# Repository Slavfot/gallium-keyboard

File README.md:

## Gallium Keyboard

The Gallium Keyboard is a Wireless Ergonomical Split Keyboard.

# DISCLAIMER

I have a problem with the keyboard that i have opened an issue at the redox Github. https://github.com/mattdibi/redox-keyboard/issues/55
The problem is interference making it hard to use in some environments.
I use it daily at work and it works really good except sometimes i have to replug the usb receiver at startup to get a good connection.
At home it is almost unusable because of interference. Missing key presses and high latency.
I'm trying to solve this and will post an update when i find a stable solution for the wireless communication.

# Future
At the moment I'm working on a micro pro version wich will make it possible to use the nice!nano bluetooth module with it instead.
My goal is to stock these and sell as kits togehter with 3D printed case. And even aluminium cases in GB.

## Summary

  - [Bill of materials](#bill-of-materials)
  - [Transmitters Assembly](#transmitters-assembly)
  - [Receiver Assembly](#receiver-assembly)
  - [Firmware](#firmware)
  - [Battery usage](#battery-usage)

## Bill of materials

#### Transmitters

| Qty | Item                                          | Notes                                               |
|----:|-----------------------------------------------|-----------------------------------------------------|
|  62 | Cherry MX compatible switches                 |                                                     |
|  62 | Kailh MX hot swap sockets (optional)          |                                                     |
|   2 | Gallium Wireless PCBs                         |                                                     |
|   2 | YJ-14015 modules (Core51822B clones)          | [aliexpress or ebay](https://www.aliexpress.com/item/NRF51822-Core51822-BLE-4-0-Bluetooth-2-4G-Wireless-Module-Antenna-Board-For-ULP-SPI-I2C/32842154172.html?spm=2114.search0104.3.8.663a616aYeRlVr&ws_ab_test=searchweb0_0,searchweb201602_1_10065_10068_10843_10059_10884_10887_10696_100031_10084_10083_10103_10618_10304_10307_10820_10821_10302,searchweb201603_60,ppcSwitch_5&algo_expid=1dded059-5054-4890-bcc4-6face1150a21-1&algo_pvid=1dded059-5054-4890-bcc4-6face1150a21&priceBeautifyAB=0)
|  62 | 1N4148 diodes                                 | SMD 1N4148 SOD-123 diodes can also be used          |
|   2 | Keystone 3034 SMT battery holders             | [digikey](https://www.digikey.com/product-detail/en/keystone-electronics/3034/36-3034-ND/4499289)|
|   2 | PCM12SMTR SMT slide switches                  | [digikey](https://www.digikey.com/product-detail/en/c-k/PCM12SMTR/401-2016-1-ND/1640125)|
|   2 | Right angle 0.1" header (1x4pin)              |                                                     |

#### Receiver

| Qty | Item                                          | Notes                                               |
|----:|-----------------------------------------------|-----------------------------------------------------|
|   1 | Redox receiver PCB                            |                                                     |
|   1 | YJ-14015 module (Core51822B clone)            | [aliexpress or ebay](https://www.aliexpress.com/item/NRF51822-Core51822-BLE-4-0-Bluetooth-2-4G-Wireless-Module-Antenna-Board-For-ULP-SPI-I2C/32842154172.html?spm=2114.search0104.3.8.663a616aYeRlVr&ws_ab_test=searchweb0_0,searchweb201602_1_10065_10068_10843_10059_10884_10887_10696_100031_10084_10083_10103_10618_10304_10307_10820_10821_10302,searchweb201603_60,ppcSwitch_5&algo_expid=1dded059-5054-4890-bcc4-6face1150a21-1&algo_pvid=1dded059-5054-4890-bcc4-6face1150a21&priceBeautifyAB=0) |
|   1 | Arduino 5v 16MHz Pro Micro compatible microcontroller  | [aliexpress or ebay]                                |
|   1 | 1117 3.3v regulator in SOT223                 | [digikey](https://www.digikey.com/product-detail/en/diodes-incorporated/AZ1117IH-3.3TRG1/AZ1117IH-3.3TRG1DICT-ND/5699682)|
|   2 | 330 Ohm 0805(2012 metric) SMD resistors       | Default configuration. Values depends on LED color, see [below](#resistor-values)|
|   2 | 220 Ohm 0805(2012 metric) SMD resistors       | Default configuration. Values depends on LED color, see [below](#resistor-values)|
|   3 | 1.5k Ohm 0805(2012 metric) SMD resistors      | Default configuration. See [below](#resistor-values)|
|   1 | Red 0805(2012 metric) SMD standard LED        | Default configuration.                              |
|   1 | Blue 0805(2012 metric) SMD standard LED       | Default configuration.                              |
|   1 | Green 0805(2012 metric) SMD standard LED      | Default configuration.                              |
|   1 | White 0805(2012 metric) SMD standard LED      | Default configuration.                              |
|   1 | Through hole momentary switch                 | Dimensions 6mm x 6mm x 4.3mm                        |
|   1 | Right angle 0.1" header (1x4pin)              |                                                     |
|   2 | Straight hot swap 0.1" header (1x6pin)        | Use wire from diods as legs                         |

> :information_source: You can also use the [Mitosis receiver](https://github.com/reversebias/mitosis-hardware/blob/master/bom/README.md) since it's almost identical, or you can build a receiver on your own. 

> :warning: To program the YJ-14015 MCUs you need an ST-Link v2 programmer, these can be found on eBay or Aliexpress for as little as 2$ shipped. See [picture below](#nordic-mcus-firmware).

##### Resistor values

If you want to customize your LEDs color or save a few bucks by ordering the LED all the same color you can refer to this section for choosing the correct resistor values. Otherwise you can refer to the [default configuration](#default-configuration).

There are two sets of resistor that you need for the receiver.

- The voltage divider resistors (`R1`, `R2` and `R3`): anything between 1.5k Ohm and 4.7k Ohm is good.
- The LEDs resistors (`R4`,`R6`,`R7` and `R8`): see the following table.

| LED color | Vf   | Suggested resistor value |
|-----------|------|--------------------------|
| Red       | 1.7V | 330 Ohm                  |
| Yellow    | 2.1V | 330 Ohm                  |
| Blue      | 3.2V | 220 Ohm                  |
| Green     | 2.2V | 330 Ohm                  |
| White     | 3.6V | 220 Ohm                  |

Depending on the color you choose to use you should use the resistor listed above.

#### Default configuration

Here you can find the default configuration for the receiver assembly.

| Label | Component         |
|-------|-------------------|
| D1    | Red LED           |
| D2    | Blue LED          |
| D3    | Green LED         |
| D4    | White LED         |
| R4    |  330 Ohm resistor |
| R6    |  220 Ohm resistor |
| R7    |  330 Ohm resistor |
| R8    |  220 Ohm resistor |
| R1    | 1.5k Ohm resistor |
| R2    | 1.5k Ohm resistor |
| R3    | 1.5k Ohm resistor |

## Transmitters Assembly

Assembly steps:

- Solder components to PCBs.
  1. Solder slider switch. 
  2. Solder the YJ-14015 on the same side as the slider switch.
  3. Solder 1N4148 diodes either SMT or THT (Surface-mount Technology or Through-hole Technology).
  4. Apply insulating tape over the pads surrounding the battery ground pad before soldering the battery holder [picture below](#battery-holder-installation-detail).
  5. Some solder is needed on the ground pad to contact properly with the battery. See [picture below](#battery-holder-installation-detail).
  6. Solder the battery holders.
  7. If you use the onboard CR2032 battery holder then bridge the jumper JP_BAT1 to either R or L depending on wich side the battery is located on. See [picture below](#bridge-jumper).
     (This is not needed if you use external battery pinout EXT-BAT)
  8. Solder the programming headers.
  9. (Optional) Solder Kailh Hot Swap Sockets
- Fit the PCBs inside their cases.
- Add the switches to the plate.
- Solder switches to the PCB.
- Add the CR2032 batteries.
- Program the MCUs.
- Close the case.

##### How i solder surface mount components:
Wet one pad with solder.
Position the component and hold the component in place with a tweezer.
Heat up the wet pad and let cool, this should fix the component.
Re-heat and adjust the position if the component isn't placed perfect.
Be sure not to heat to long wich may damage the PCB or the component.
Solder the rest of the pads like normal.

##### Programming headers detail:

##### MCUs detail:

##### Slider switch detail:

##### Diodes installation detail:

SMT on the left and THT on the right.

##### Battery holder installation detail:

##### Left and right hand completed assembly:

##### Assembled PCB:

## Receiver Assembly

The receiver assembly is pretty straightforward i suggest soldering it in this order:

1. Solder D1, D2, D3 and D4 LEDs. See [image](#leds-installation-detail) for orientation.
2. Solder R4, R6, R7 and R8 resistors.
3. Solder R1, R2 and R3 resistors.
4. Solder the AMS1117.
5. Solder the programming headers. I suggest you to cut the excess of the header **before** soldering the headers. You should stay as flush to the PCB surface as possible since the controller will be soldered above the headers. Use some masking tape to help you keep the header in place while soldering.
6. Solder the Arduino Pro Micro headers.
7. Solder the YJ-14015. I suggest you to glue it in place or use some masking tape to help you during soldering.
8. Solder the reset button.
9. Upload the firmware and you're done.

##### Assembled PCB, front:

##### Assembled PCB, back:

##### LEDs installation detail:

> :information_source: Please note that here I installed 220 Ohm resistors because I used only blue and white LEDs as I only had those laying around. You should use the resistor values suggested [here](#resistor-values) or follow the [default configuration](#default-configuration).

## Firmware

**Basics**: The Gallium keyboard works similarly to the [Mitosis keyboard](https://github.com/qmk/qmk_firmware/tree/master/keyboards/mitosis): we have two transmitters responsible for scanning the two matrices, which then transmit the matrix status through the [Gazel protocol](https://developer.nordicsemi.com/nRF5_SDK/nRF51_SDK_v5.x.x/doc/5.2.0/html/a00140.html) to the receiver. The receiver is another YJ-14015 which receives the two matrix scans and send it through serial to the Arduino Pro Micro. The Pro Micro is responsible for running QMK and converting the bytes received by the YJ-14015 into actual keystrokes.

Firmware sources available here: [https://github.com/slavfot/gallium-firmware](https://github.com/slavfot/gallium-firmware).

You'll need to upload the firmware to the corresponding MCUs as per the following diagram:

Note that you'll need to upload the firmware for the YJ-14015 only once. Everything related to the keymap is handled by the Arduino Pro Micro and QMK Firmware, that's what you will need to modify to update the keymap.

### Step-by-step firmware upload guide

#### Arduino Pro Micro Firmware upload

Let's start by uploading the QMK firmware on the Arduino, this will help us in diagnosing problems early on. The Gallium uses QMK for its firmware, follow the QMK installation instructions [here](https://docs.qmk.fm/#/getting_started_build_tools), then compile and burn the firmware as follows:

```sh
$ cd path/to/qmk_firmware
$ make gallium:default:avrdude
```

You can find the code for the Gallium here: [QMK - Gallium Wireless keyboard](https://github.com/slavfot/qmk_firmware/tree/gallium/keyboards/gallium).

In the [Gallium Keyboard firmware repository](https://github.com/slavfot/gallium-firmware/tree/master/precompiled) I added some pre-built hex files with the default keymap for testing purpose.

#### Nordic MCUs Firmware upload

You'll need only to flash the pre-built `.hex` files to the corresponding MCUs, for this you'll need an STLinkV2 debugger.

# Flashing firmware with Windows

## Setup the environment

##### 1. Activate Telnet Client in windows:

- Open the Control Panel - with View By: Category.
- Click on Programs.
- Click on Turn Windows features on or off.
- Click on the checkbox next to Telnet client.
- Click OK.

##### 2. Download pre-compiled openOCD
https://freddiechopin.info/en/download/category/4-openocd <br>
Unzip anywhere. 
But for ease of use in CMD i put it in C:\OpenOCD

## Flash with CMD

###### 1. Hook up the receiver/keyboard half

Hook up the ST-Link debugger to the receiver/keyboard board you assembled without the Arduino. You need to connect only the `VCC`, `GND`, `SWDIO` and `SWCLK` pins of the board like this:

| ST-Link Debugger | Receiver board |
|------------------|----------------|
|       3.3V       |       VCC      |
|        GND       |       GND      |
|       SWCLK      |      SWCLK     |
|       SWDIO      |      SWDIO     |

Then plug in the ST-Link debugger into your PC.

##### 2. Launch CMD.

##### 3. With terminal commands position the CMD in 
```
\openOCD\bin
```
First make sure you are in the right drive.
If you need to change drive then type the drive letter only likes this "d:" <br>
after that you can navigate in that drive.

Commands to navigate with:

- cd (change directory)
- cd .. (go back one directory)
- dir (show all the directorys in the folder you are located in)

Tips: Press the tab button to automaticaly complete the directorys name while typing the cd command.

##### 4. Download Gallium-keyboard repository
Download Gallium-keyboard master zip and unzip anywhere but for ease of use put it in C:\
https://github.com/Slavfot/gallium-keyboard/archive/master.zip

##### 5. Launch CMD
Launch an openOCD server session with this command:

```sh
openocd -s C:\OpenOCD\scripts\ -f interface/stlink-v2.cfg -f target/nrf51.cfg
```

This line is written as if the OpenOCD folder is located at C:\ <br>
Change accordingly to where you have it located.

It should give you an output ending in:

```
Info : nrf51.cpu: hardware has 4 breakpoints, 2 watchpoints
```
Otherwise you likely have a loose or wrong wire.

##### 6. Launch another CMD window.

##### 7. cd to the location where the hex is located.

Example for the file path if the .hex file is located in C:\Gallium-keyboard\precompiled

/gallium-keyboard/precompiled/

##### 8. Run these commands in the new window, wait for each command to finish until you run the next command.
Connect to the OpenOCD session:
```
telnet localhost 4444
```
From the factory, these chips need to be erased:
```sh
reset halt

nrf51 mass_erase
```
Write file to wireless-module

Use this command to flash the receiver:
```sh
flash write_image /gallium-keyboard/precompiled/precompiled-basic-receiver.hex
```
For each keyboard half flash with either of these files
```sh
flash write_image /gallium-keyboard/precompiled/precompiled-basic-left.hex
```
or
```sh
flash write_image /gallium-keyboard/precompiled/precompiled-basic-right.hex
```

This is how it should look when you connect to telnet:

The whole process should look like this:

##### 9. Repeat untill you have flashed all three wireless modules.

##### 10. End openOCD sessionen with ctrl+C in the first CMD window.
Congratulations you have now flashed your Gallium Keyboard!

# Firmware upload using Linux

*Note*: Tested on Ubuntu 16.04 and 18.04 but you should be able to find alternatives on all distros.

##### Setup

###### Install OpenOCD (Open On-Chip Debugger)

```sh
sudo apt update
sudo apt install openocd
```

###### Download the repository

Open a terminal and download this repository wherever you want. We'll need the `gallium/firmware` folder content.

```sh
git clone https://github.com/slavfot/gallium-keyboard.git
```

or

```sh
wget https://github.com/slavfot/gallium-keyboard/archive/master.zip
```

###### Install the udev rules

```sh
cd path/to/repository/gallium-keyboard/firmware/
sudo cp 49-stlinkv2.rules /etc/udev/rules.d/
```

##### Programming the wireless modules Using Linux

###### Hook up the receiver/keyboard half

Hook up the ST-Link debugger to the receiver/keyboard board you assembled without the Arduino. You need to connect only the `VCC`, `GND`, `SWDIO` and `SWCLK` pins of the board like this:

| ST-Link Debugger | Receiver board |
|------------------|----------------|
|       3.3V       |       VCC      |
|        GND       |       GND      |
|       SWCLK      |      SWCLK     |
|       SWDIO      |      SWDIO     |

Then plug in the ST-Link debugger into your PC.

###### Launch an OpenOCD server session

In a new terminal window launch an OpenOCD server session by issuing the following command:

```sh
openocd -s /usr/local/Cellar/open-ocd/0.8.0/share/openocd/scripts/ -f interface/stlink-v2.cfg -f target/nrf51.cfg
```

This should give the following output:

```sh
Info : nrf51.cpu: hardware has 4 breakpoints, 2 watchpoints
```

Leave this terminal window open.

###### Wireless-module firmware flashing

There are three Wireless modules that need to be flashed with firmware:
The receiver, left hand keyboard hand the right hand keyboard.

We can now issue the flashing commands. Open a terminal in the Gallium firmware folder.

```sh
cd path/to/repository/gallium-keyboard/firmware/
```

From the factory, these chips need to be erased:

```sh
echo reset halt | telnet localhost 4444
echo nrf51 mass_erase | telnet localhost 4444
```

You should be seeing some movement in the OpenOCD terminal window, and you desktop should be looking somewhat like this:

Now we can upload the receiver firmware onto the MCU.

```sh
echo reset halt | telnet localhost 4444

!Choose one!:
receiver:
echo flash write_image `readlink -f precompiled-basic-receiver.hex` | telnet localhost 4444

Left hand keyboard:
echo flash write_image `readlink -f precompiled-basic-left.hex` | telnet localhost 4444

Right hand keyboard:
echo flash write_image `readlink -f precompiled-basic-right.hex` | telnet localhost 4444

and last:
echo reset | telnet localhost 4444
```

You should be looking at something like this:

Now close the OpenOCD session (use `Ctrl-C`) and you're done with the flashing. Repeat these steps for all three modules.

When all three modules have been flash you are done!
Congratulations, You flashed the Gallium Keyboard!

## Battery usage

mattdibi about the battery consumption:

With a CR2032 with 220mAh we can expect **at least 880 hours** of continuous typing on the keyboard before needing to change the batteries. Keep in mind that when you're not typing (500ms without key presses is the time interval needed for the keyboard) the transmitters go into deep sleep mode and draw only 2.7uA. So for an everyday use (4 hours a day of continuous typing) you can expect a battery life of at least a year. Obviously your mileage may vary.
Source and calculations: https://github.com/mattdibi/redox-keyboard/tree/master/redox-w#battery-usage

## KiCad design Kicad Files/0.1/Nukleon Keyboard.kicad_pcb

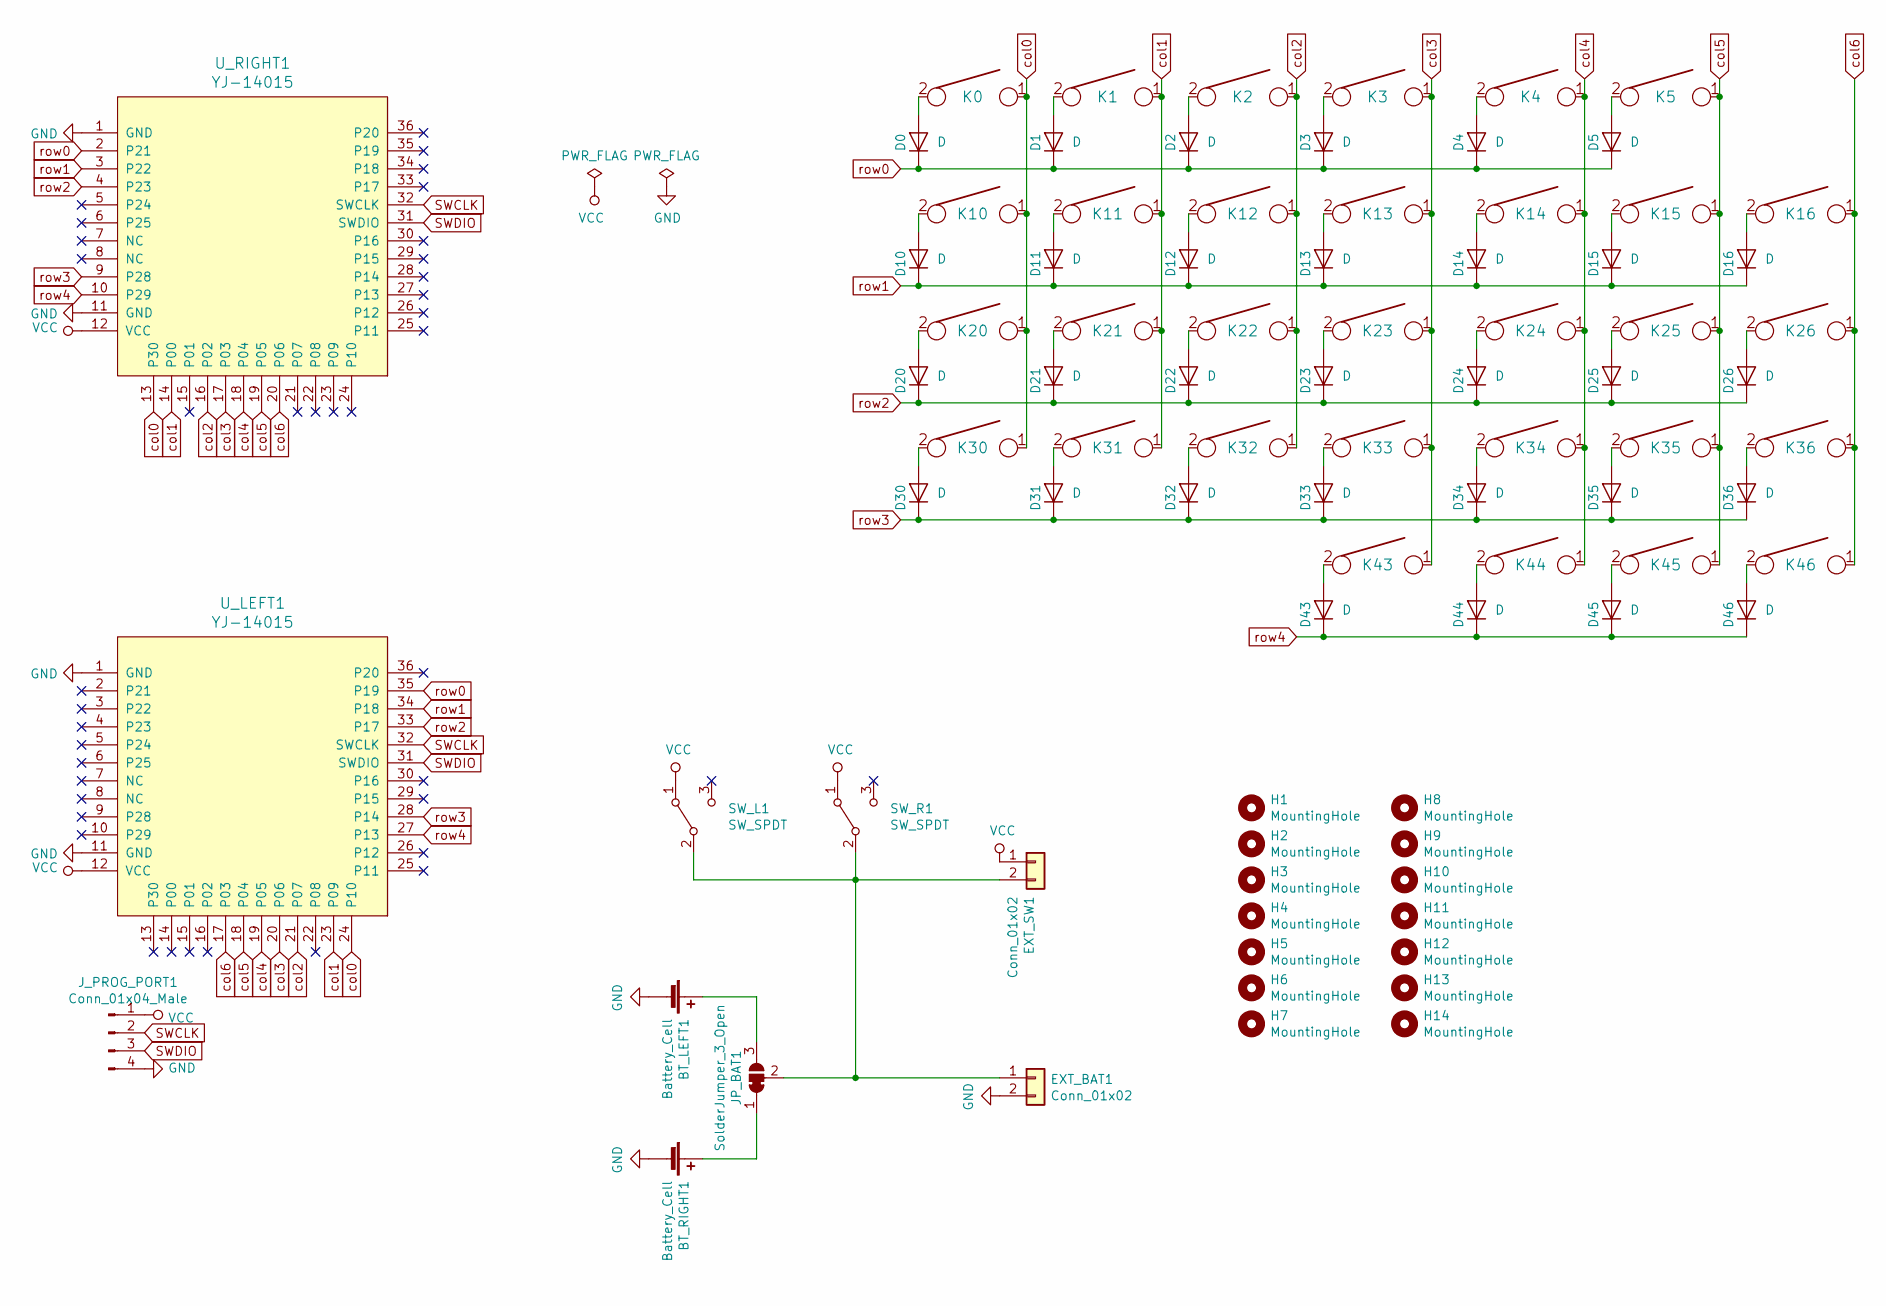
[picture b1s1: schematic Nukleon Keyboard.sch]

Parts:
BT_LEFT1: Battery_Cell; BatteryHolder_Keystone_3034_1x20mm_left
BT_RIGHT1: Battery_Cell; BatteryHolder_Keystone_3034_1x20mm_right
D0, D1, D2, D3, D4, D5, D10, D11, D12, D13, D14, D15, D16, D20, D21, D22, D23, D24, D25, D26, D30, D31, D32, D33, D34, D35, D36, D43, D44, D45, D46: D; D_SOD123_axial_both_sides
EXT_BAT1: Conn_01x02; PinHeader_1x02_P2.54mm_Horizontal_double_side
EXT_SW1: Conn_01x02; PinHeader_1x02_P2.54mm_Horizontal_double_side
H1, H2, H3, H4, H5, H9, H10, H12, H14: MountingHole; MountingHole_2.2mm_M2_ISO7380_Pad
H6, H7, H8, H11, H13: MountingHole; Thru_hole_for_M2_standoff_space
JP_BAT1: SolderJumper_3_Open; SolderJumper-3_P1.3mm_Open_RoundedPad1.0x1.5mm_NumberLabels
J_PROG_PORT1: Conn_01x04_Male; PinHeader_1x04_P2.54mm_Horizontal
K0, K1, K2, K3, K4, K5, K10, K11, K12, K13, K14, K15, K16, K20, K21, K22, K23, K24, K25, K26, K30, K31, K32, K33, K34, K35, K36: KEYSW; SW_Cherry_MX_1.00u_PCB_Hot_Swap_Optional
K43, K44, K45, K46: KEYSW; PG1350_socket_reversible_MX_Holtite
SW_L1: SW_SPDT; SW_SPDT_PCM12
SW_R1: SW_SPDT; SW_SPDT_PCM12
U_LEFT1: YJ-14015; MY-YJ-14015-Module
U_RIGHT1: YJ-14015; MY-YJ-14015-Module

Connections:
GND: BT_LEFT1.2 (-), BT_RIGHT1.2 (-), EXT_BAT1.2, J_PROG_PORT1.4, U_LEFT1.1 (GND), U_LEFT1.11 (GND), U_RIGHT1.1 (GND), U_RIGHT1.11 (GND)
unnamed: BT_LEFT1.1 (+), JP_BAT1.3 (B)
unnamed: BT_RIGHT1.1 (+), JP_BAT1.1 (A)
unnamed: D0.2 (A), K0.2
unnamed: D1.2 (A), K1.2
unnamed: D2.2 (A), K2.2
unnamed: D3.2 (A), K3.2
unnamed: D4.2 (A), K4.2
unnamed: D5.2 (A), K5.2
unnamed: D10.2 (A), K10.2
unnamed: D11.2 (A), K11.2
unnamed: D12.2 (A), K12.2
unnamed: D13.2 (A), K13.2
unnamed: D14.2 (A), K14.2
unnamed: D15.2 (A), K15.2
unnamed: D16.2 (A), K16.2
unnamed: D20.2 (A), K20.2
unnamed: D21.2 (A), K21.2
unnamed: D22.2 (A), K22.2
unnamed: D23.2 (A), K23.2
unnamed: D24.2 (A), K24.2
unnamed: D25.2 (A), K25.2
unnamed: D26.2 (A), K26.2
unnamed: D30.2 (A), K30.2
unnamed: D31.2 (A), K31.2
unnamed: D32.2 (A), K32.2
unnamed: D33.2 (A), K33.2
unnamed: D34.2 (A), K34.2
unnamed: D35.2 (A), K35.2
unnamed: D36.2 (A), K36.2
unnamed: D43.2 (A), K43.2
unnamed: D44.2 (A), K44.2
unnamed: D45.2 (A), K45.2
unnamed: D46.2 (A), K46.2
unnamed: EXT_BAT1.1, EXT_SW1.2, JP_BAT1.2 (C), SW_L1.2 (B), SW_R1.2 (B)
SWCLK: J_PROG_PORT1.2, U_LEFT1.32 (SWCLK), U_RIGHT1.32 (SWCLK)
SWDIO: J_PROG_PORT1.3, U_LEFT1.31 (SWDIO), U_RIGHT1.31 (SWDIO)
VCC: EXT_SW1.1, J_PROG_PORT1.1, SW_L1.1 (A), SW_R1.1 (A), U_LEFT1.12 (VCC), U_RIGHT1.12 (VCC)
col0: K0.1, K10.1, K20.1, K30.1, U_LEFT1.24 (P10), U_RIGHT1.13 (P30)
col1: K1.1, K11.1, K21.1, K31.1, U_LEFT1.23 (P09), U_RIGHT1.14 (P00)
col2: K2.1, K12.1, K22.1, K32.1, U_LEFT1.21 (P07), U_RIGHT1.16 (P02)
col3: K3.1, K13.1, K23.1, K33.1, K43.1, U_LEFT1.20 (P06), U_RIGHT1.17 (P03)
col4: K4.1, K14.1, K24.1, K34.1, K44.1, U_LEFT1.19 (P05), U_RIGHT1.18 (P04)
col5: K5.1, K15.1, K25.1, K35.1, K45.1, U_LEFT1.18 (P04), U_RIGHT1.19 (P05)
col6: K16.1, K26.1, K36.1, K46.1, U_LEFT1.17 (P03), U_RIGHT1.20 (P06)
row0: D0.1 (K), D1.1 (K), D2.1 (K), D3.1 (K), D4.1 (K), D5.1 (K), U_LEFT1.35 (P19), U_RIGHT1.2 (P21)
row1: D10.1 (K), D11.1 (K), D12.1 (K), D13.1 (K), D14.1 (K), D15.1 (K), D16.1 (K), U_LEFT1.34 (P18), U_RIGHT1.3 (P22)
row2: D20.1 (K), D21.1 (K), D22.1 (K), D23.1 (K), D24.1 (K), D25.1 (K), D26.1 (K), U_LEFT1.33 (P17), U_RIGHT1.4 (P23)
row3: D30.1 (K), D31.1 (K), D32.1 (K), D33.1 (K), D34.1 (K), D35.1 (K), D36.1 (K), U_LEFT1.28 (P14), U_RIGHT1.9 (P28)
row4: D43.1 (K), D44.1 (K), D45.1 (K), D46.1 (K), U_LEFT1.27 (P13), U_RIGHT1.10 (P29)

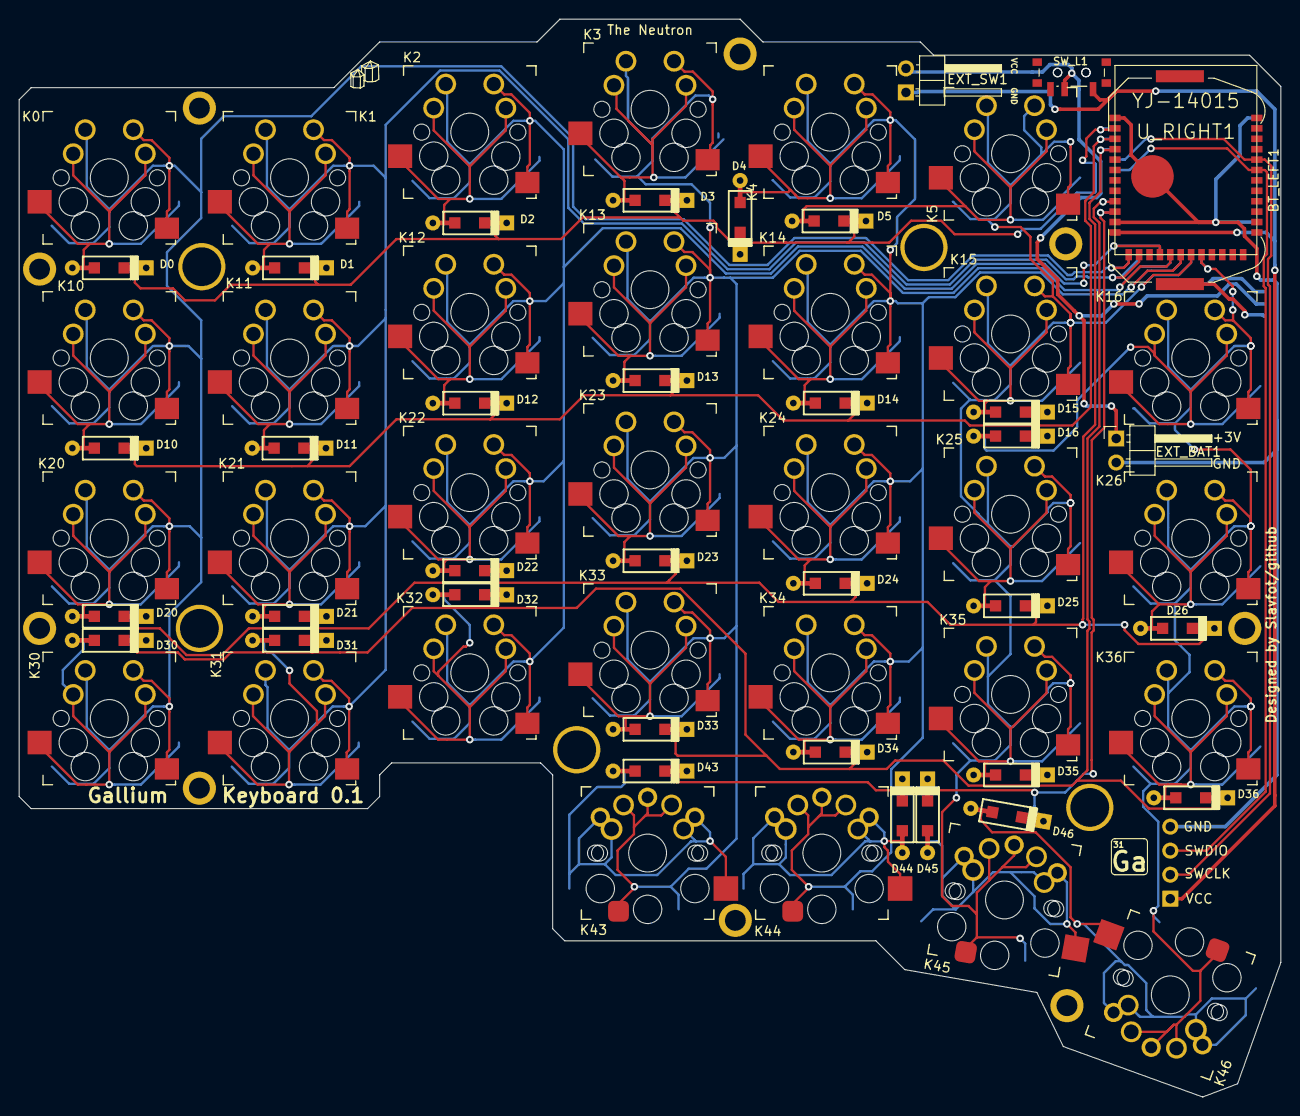
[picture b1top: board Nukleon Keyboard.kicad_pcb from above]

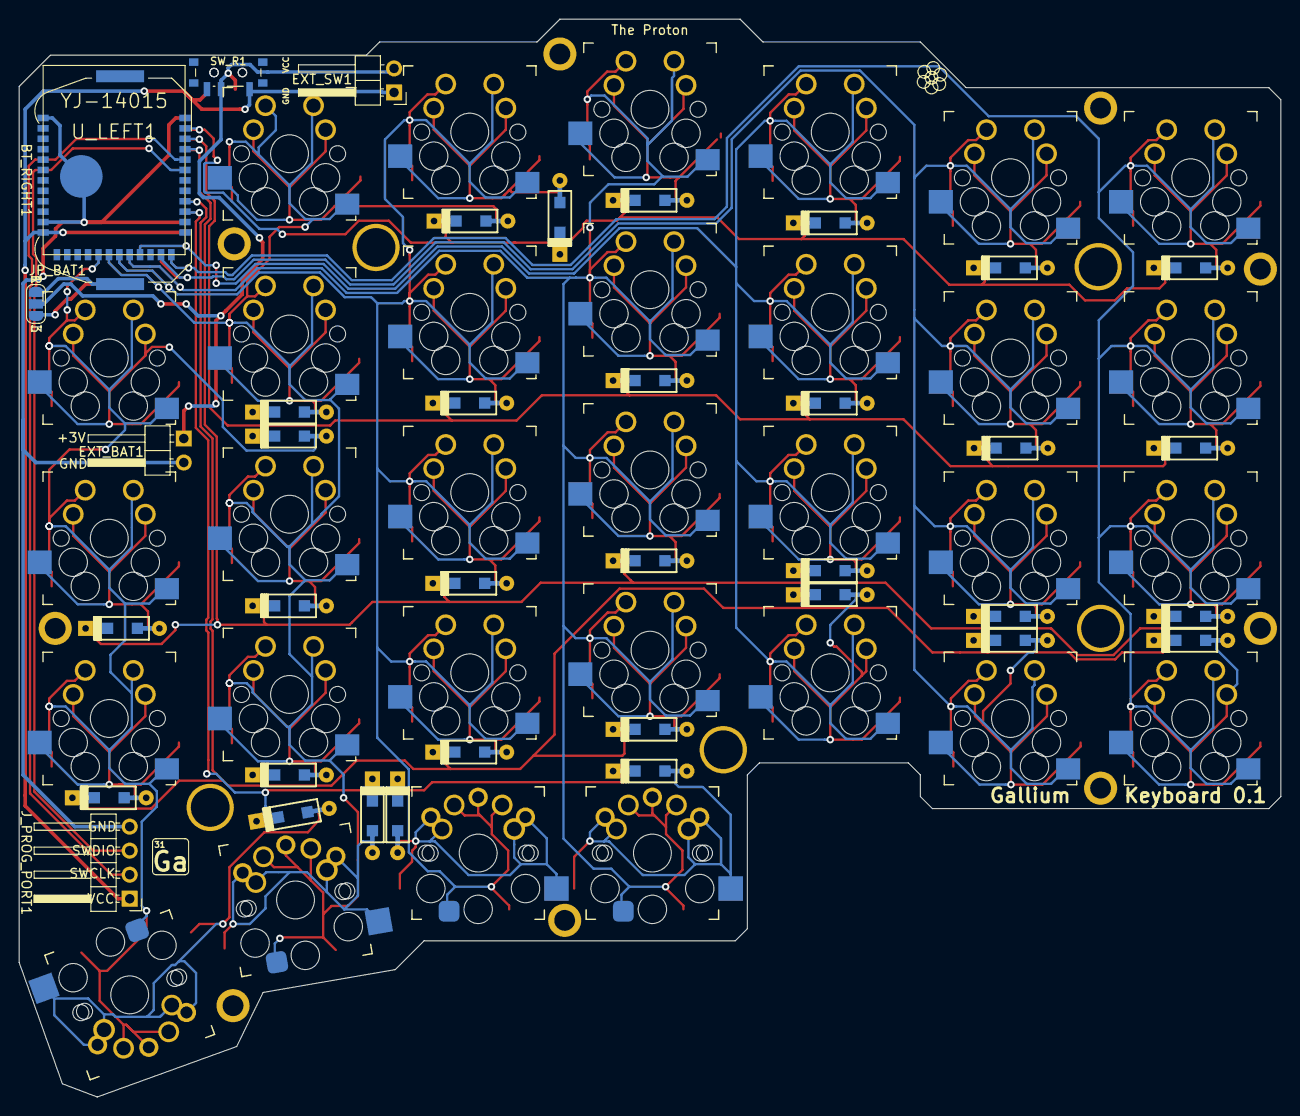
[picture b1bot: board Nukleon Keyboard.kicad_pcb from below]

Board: 2 copper layers, 133.3 x 113.9 mm, 86 parts (6 on the bottom side), 50 nets.

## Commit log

2020-06-22 Firsty Try!
2020-06-22 fixa filnamn
2020-06-22 fix pathway to img+added img
2021-02-04 Updated Receiver Assembly
    Updated Receiver Assembly Order
2021-02-04 added kicad files
    added kicad files
2021-02-04 Added STL
    Added STL for case revision 0.1
    Added plate file .dxf for revision 0.1
2021-02-04 Updated readme
    Updated readme with disclaimer and future
